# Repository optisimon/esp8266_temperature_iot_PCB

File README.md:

# esp8266_temperature_iot_PCB

This is the PCB portion of the temperature plotting iot project.

Project homepage: https://optisimon.com/esp8266/arduino/temperature/monitoring/2020/01/07/esp8266-temperature-plotting-iot/

Software portion: https://github.com/optisimon/esp8266_temperature_iot

Hardware portion: https://github.com/optisimon/esp8266_temperature_iot_PCB/

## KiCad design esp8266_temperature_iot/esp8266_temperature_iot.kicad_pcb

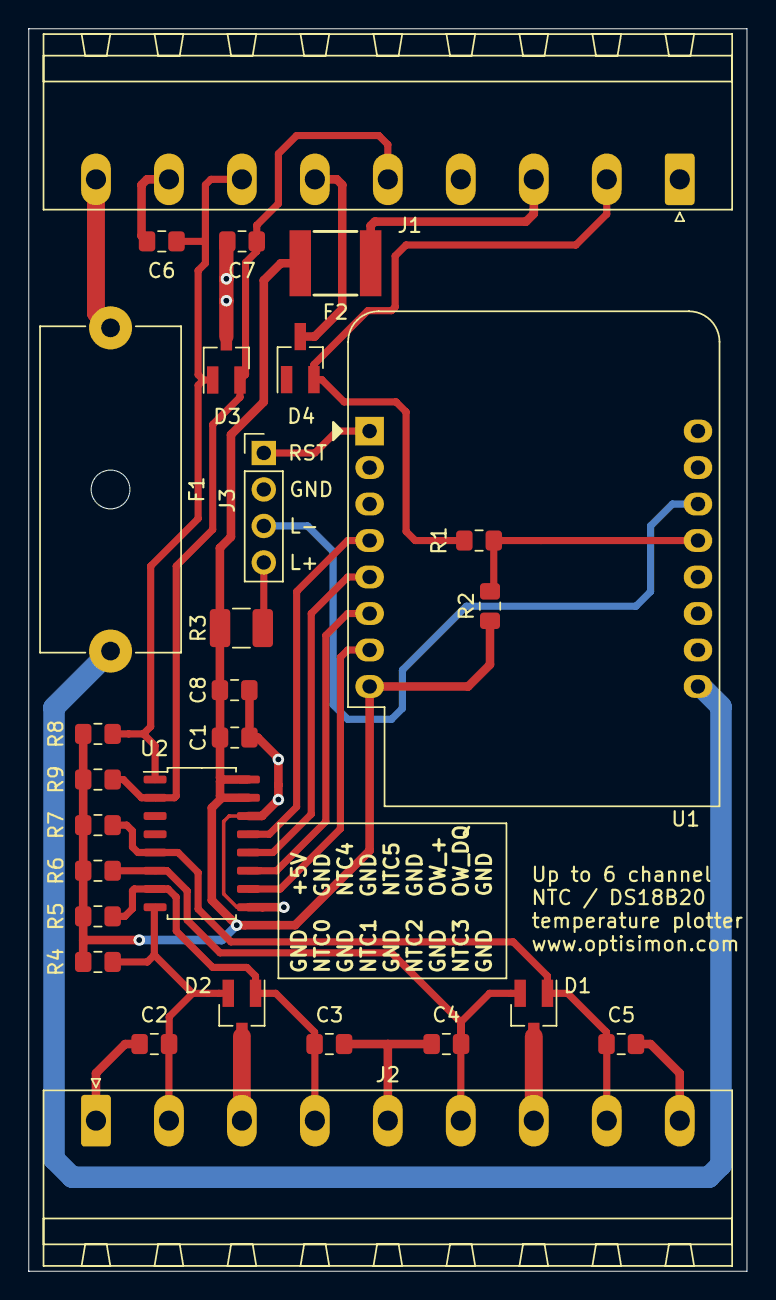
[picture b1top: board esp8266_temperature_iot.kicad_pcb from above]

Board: 2 copper layers, 50.0 x 86.5 mm, 28 parts (0 on the bottom side), 20 nets.

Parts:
C1, C2, C3, C4, C5, C6, C7: 100nF; C_0805_2012Metric_Pad1.15x1.40mm_HandSolder
C8: 1uF; C_0805_2012Metric_Pad1.15x1.40mm_HandSolder
D1, D2, D3, D4: PESD3V3L2BT; SOT-23_Handsoldering
F1: Fuse; Fuseholder_Cylinder-5x20mm_Schurter_0031_8201_Horizontal_Op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
F2: Polyfuse_Small; Fuse_Littlefuse-2016L
J1, J2: Screw_Terminal_01x09; PhoenixContact_MSTBA_2,5_9-G-5,08_1x09_P5.08mm_Horizontal
J3: Conn_01x04_Male; PinHeader_1x04_P2.54mm_Vertical
R1: 270; R_0805_2012Metric_Pad1.15x1.40mm_HandSolder
R2: 4k7; R_0805_2012Metric_Pad1.15x1.40mm_HandSolder
R3: 1k; R_1210_3225Metric_Pad1.42x2.65mm_HandSolder
R4, R5, R6, R7, R8, R9: 10k; R_0805_2012Metric_Pad1.15x1.40mm_HandSolder
U1: WeMos_D1_mini; WEMOS_D1_mini_light
U2: MCP3208; SOIC-16_4.55x10.3mm_P1.27mm

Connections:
+3V3: C1.1, C8.1, F2.2, R2.1, R3.2, R4.1, R5.1, R6.1, R7.1, R8.1, R9.1, U1.8, U2.15, U2.16
+5V: F1.2, U1.9
Earth: C1.2, C2.1, C3.1, C4.1, C5.1, C6.1, C7.1, C8.2, D1.3, D2.3, D3.3, D4.3, J1.1, J1.4, J1.6, J1.8, J2.1, J2.3, J2.5, J2.7, J2.9, J3.2, U1.10, U2.9, U2.14
LED1: J3.3, U1.14
MISO: U1.5, U2.12
MOSI: U1.6, U2.11
NTC0: C2.2, D2.2, J2.2, R4.2, U2.8
NTC1: C3.2, D2.1, J2.4, R5.2, U2.7
NTC2: C4.2, D1.2, J2.6, R6.2, U2.6
NTC3: C5.2, D1.1, J2.8, R7.2, U2.5
NTC4: C6.2, D3.1, J1.7, R8.2, U2.1
NTC5: C7.2, D3.2, J1.5, R9.2, U2.2
unnamed: F1.1, J1.9
unnamed: J3.1, U1.1
unnamed: J3.4, R3.1
OneWire_+: F2.1, J1.3
OneWire_DQ: R1.1, R2.2, U1.13
OneWire_DQ_EXT: D4.2, J1.2, R1.2
SCLK: U1.4, U2.13
nCS: U1.7, U2.10

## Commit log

2019-12-04 Schematic and rough routing
2019-12-05 Nicer looking PCB (thicker wires + ground pour)
2019-12-05 Even nicer - everything double checked. Ready for order
2019-12-05 Adding a lib I think I can remove (since empty)
2019-12-07 Gerbers / drill file sent in order
2019-12-07 Not sure what was changed if anything
2020-01-08 Gerbers and schematic as ordered and populated
2020-01-08 README.md linking to project page and software repository
